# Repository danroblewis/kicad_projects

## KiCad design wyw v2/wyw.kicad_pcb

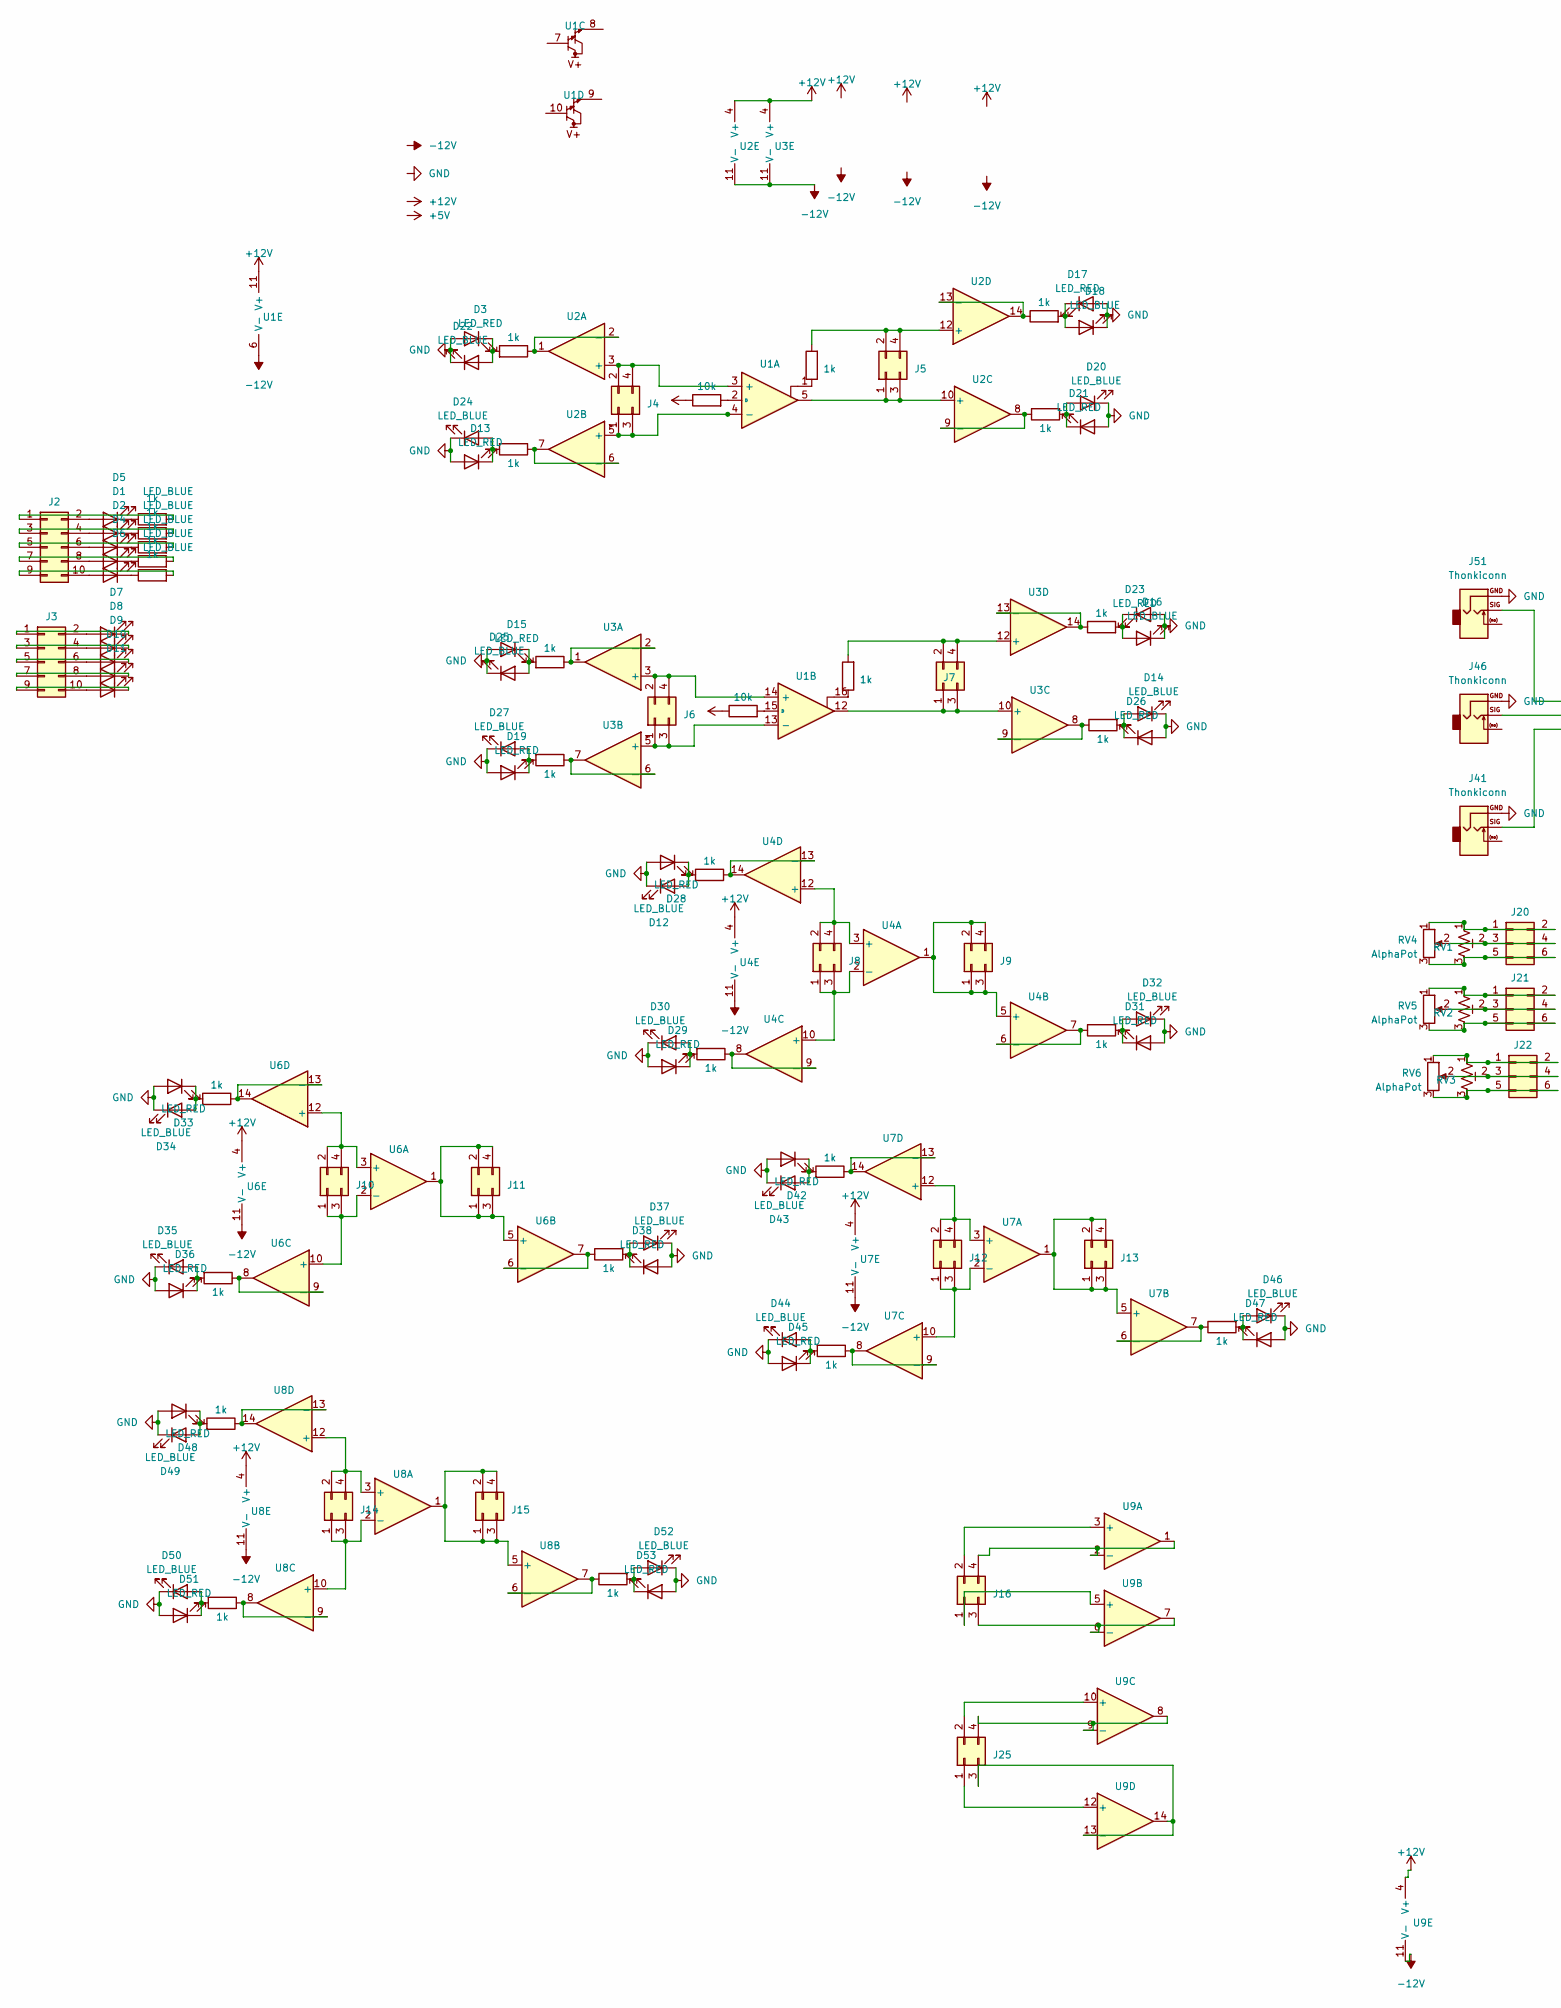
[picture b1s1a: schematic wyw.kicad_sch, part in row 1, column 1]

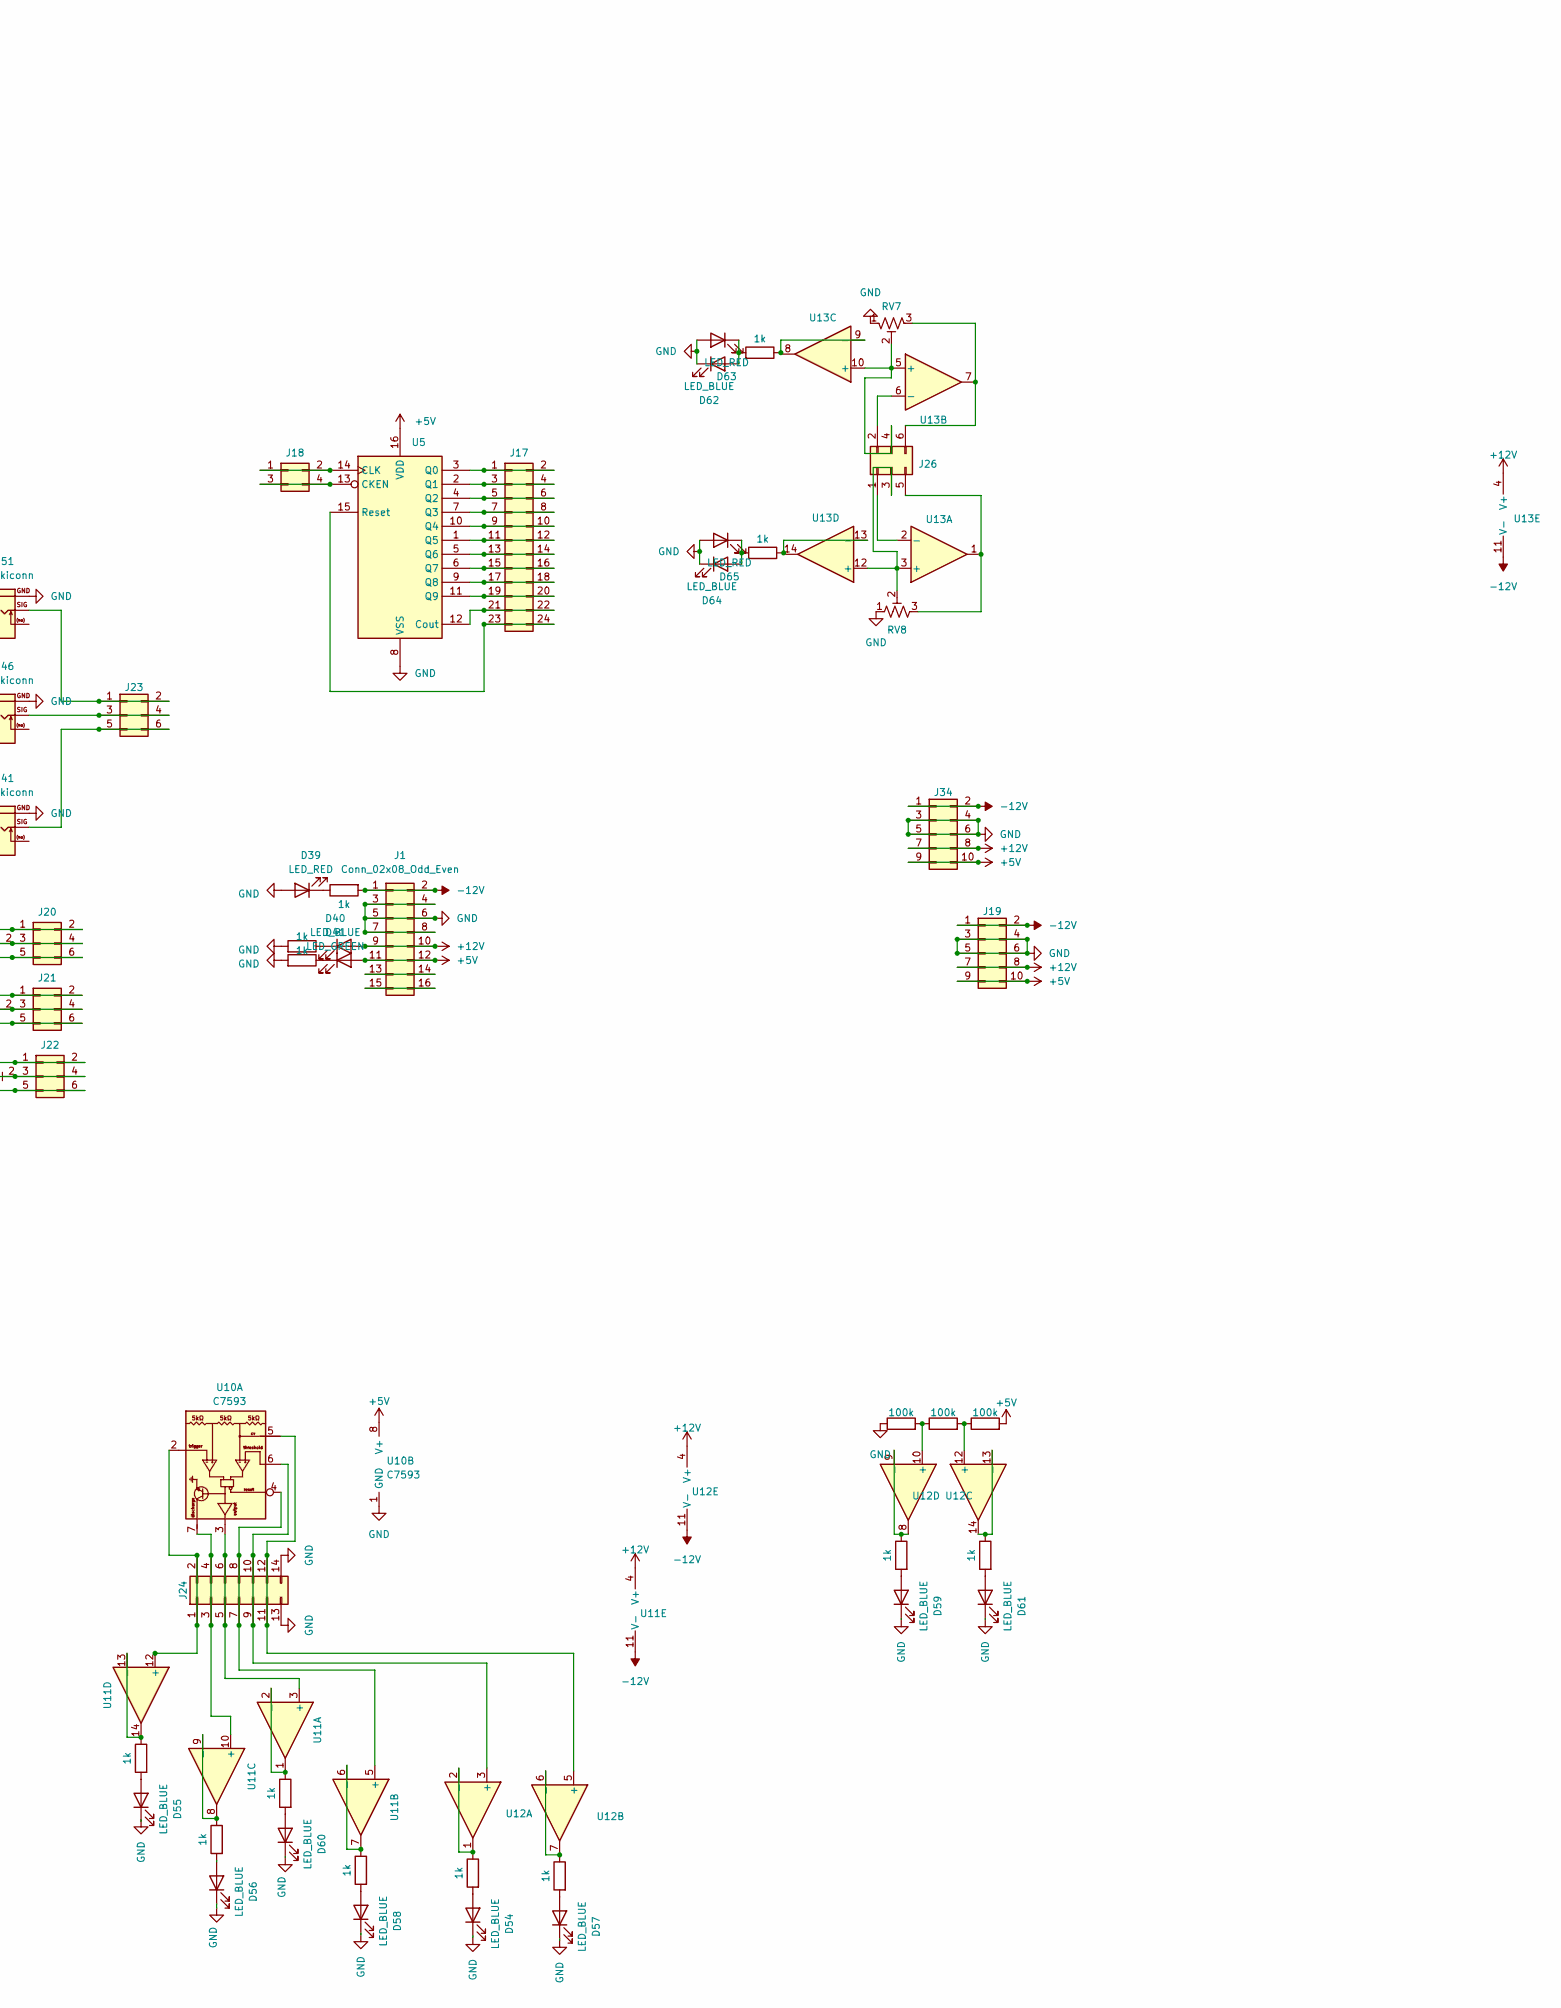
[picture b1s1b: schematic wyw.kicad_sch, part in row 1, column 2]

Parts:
D1, D2, D4, D5, D6, D7, D8, D9, D10, D11, D40: LED_BLUE; LED_0603_1608Metric; LCSC C72041
D3, D13, D15, D17, D19, D21, D23, D26, D28, D29, D31, D33, D36, D38, D42, D45, D47, D48, D51, D53, D63, D65: LED_RED; LED_0201_0603Metric; LCSC C3646921
D12, D14, D16, D18, D20, D22, D24, D25, D27, D30, D32, D34, D35, D37, D43, D44, D46, D49, D50, D52, D54, D55, D56, D57, D58, D59, D60, D61, D62, D64: LED_BLUE; LED_0201_0603Metric; LCSC C3646921
D39: LED_RED; LED_0603_1608Metric; LCSC C84263
D41: LED_GREEN; LED_0603_1608Metric; LCSC C72043
J1: Conn_02x08_Odd_Even; IDC-Header_2x08_P2.54mm_Vertical
J2, J3, J19, J34: 02x05; PinHeader_2x05_P2.54mm_Vertical_SMD; lcsc C261072
J4, J5, J6, J7, J8, J9, J10, J11, J12, J13, J14, J15, J16, J18, J25: 02x02; PinHeader_2x02_P2.54mm_Vertical_SMD; lcsc C3975147
J17: 02x12; PinHeader_2x12_P2.54mm_Vertical_SMD; lcsc C3975157
J20, J21, J22, J23, J26: 02x03; PinHeader_2x03_P2.54mm_Vertical_SMD; lcsc C3975148
J24: 02x07; PinHeader_2x07_P2.54mm_Vertical_SMD; lcsc C84005
J41, J46, J51: Thonkiconn; Jack_3.5mm_QingPu_WQP-PJ398SM_Vertical_CircularHoles
R1, R2, R3, R4, R5, R8, R9: 1k; R_0603_1608Metric; LCSC C21190
R6, R7: 10k; R_0603_1608Metric; lcsc C73809
R10, R11, R12, R13, R14, R15, R16, R17, R18, R19, R20, R21, R22, R23, R24, R25, R26, R27, R28, R29, R30, R31, R32, R33, R34, R35, R36, R37, R38, R42, R43, R44, R45: 1k; R_0603_1608Metric; lcsc C138165
R39, R40, R41: 100k; R_0603_1608Metric; LCSC C25803
RV1, RV2, RV3, RV7, RV8: R_Potentiometer_Trim_US; Potentiometer_Bourns_TC33X_Vertical; lcsc C128545
RV4, RV5, RV6: AlphaPot; Potentiometer_Alpha_RD901F-40-00D_Single_Vertical
U1: XL13700; SOP-16_3.9x9.9mm_P1.27mm; LCSC C521166
U2, U3, U4, U6, U7, U8, U9, U11, U12, U13: TL074; SOIC-14_3.9x8.7mm_P1.27mm; lcsc C6964
U5: 4017bm; SOP-16_3.9x9.9mm_P1.27mm; LCSC C356694
U10: NE555DR; SOIC-8-1EP_3.9x4.9mm_P1.27mm_EP2.29x3mm; LCSC C7593

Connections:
+5V: D41.2 (A), J1.11, J1.12, J19.9, J19.10, J34.9, J34.10, R41.2, U5.16 (VDD), U10.8 (V+)
+12V: D40.2 (A), J1.9, J1.10, J19.7, J19.8, J34.7, J34.8, R6.1, R7.1, U1.11 (V+), U2.4 (V+), U3.4 (V+), U4.4 (V+), U6.4 (V+), U7.4 (V+), U8.4 (V+), U9.4 (V+), U11.4 (V+), U12.4 (V+), U13.4 (V+)
-12V: J1.1, J1.2, J19.1, J19.2, J34.1, J34.2, R24.2, U1.6 (V-), U2.11 (V-), U3.11 (V-), U4.11 (V-), U6.11 (V-), U7.11 (V-), U8.11 (V-), U9.11 (V-), U11.11 (V-), U12.11 (V-), U13.11 (V-)
GND: D3.2 (A), D12.1 (K), D13.2 (A), D14.1 (K), D15.2 (A), D16.1 (K), D17.2 (A), D18.1 (K), D19.2 (A), D20.1 (K), D21.2 (A), D22.1 (K), D23.2 (A), D24.1 (K), D25.1 (K), D26.2 (A), D27.1 (K), D28.2 (A), D29.2 (A), D30.1 (K), D31.2 (A), D32.1 (K), D33.2 (A), D34.1 (K), D35.1 (K), D36.2 (A), D37.1 (K), D38.2 (A), D39.2 (A), D42.2 (A), D43.1 (K), D44.1 (K), D45.2 (A), D46.1 (K), D47.2 (A), D48.2 (A), D49.1 (K), D50.1 (K), D51.2 (A), D52.1 (K), D53.2 (A), D54.1 (K), D55.1 (K), D56.1 (K), D57.1 (K), D58.1 (K), D59.1 (K), D60.1 (K), D61.1 (K), D62.1 (K), D63.2 (A), D64.1 (K), D65.2 (A), J1.3, J1.4, J1.5, J1.6, J1.7, J1.8, J19.3, J19.4, J19.5, J19.6, J24.13, J24.14, J34.3, J34.4, J34.5, J34.6, J41.S, J46.S, J51.S, R25.2, R26.2, R39.1, RV7.1, RV8.1, U5.8 (VSS), U10.1 (GND)
unnamed: D1.2 (A), J2.4
unnamed: D1.1 (K), R1.1
unnamed: D2.2 (A), J2.6
unnamed: D2.1 (K), R2.1
unnamed: D4.2 (A), J2.8
unnamed: D4.1 (K), R4.1
unnamed: D5.2 (A), J2.2
unnamed: D5.1 (K), R3.1
unnamed: D6.2 (A), J2.10
unnamed: D6.1 (K), R5.1
unnamed: D7.2 (A), J3.2
unnamed: D7.1 (K), J3.1
unnamed: D8.2 (A), J3.4
unnamed: D8.1 (K), J3.3
unnamed: D9.2 (A), J3.6
unnamed: D9.1 (K), J3.5
unnamed: D10.2 (A), J3.8
unnamed: D10.1 (K), J3.7
unnamed: D11.2 (A), J3.10
unnamed: D11.1 (K), J3.9
unnamed: D12.2 (A), D28.1 (K), R18.2
unnamed: D13.1 (K), D24.2 (A), R11.2
unnamed: D14.2 (A), D26.1 (K), R17.2
unnamed: D15.1 (K), D25.2 (A), R12.2
unnamed: D16.2 (A), D23.1 (K), R16.2
unnamed: D17.1 (K), D18.2 (A), R13.2
unnamed: D19.1 (K), D27.2 (A), R14.2
unnamed: D20.2 (A), D21.1 (K), R15.2
unnamed: D3.1 (K), D22.2 (A), R10.2
unnamed: D29.1 (K), D30.2 (A), R19.2
unnamed: D31.1 (K), D32.2 (A), R20.2
unnamed: D33.1 (K), D34.2 (A), R21.2
unnamed: D35.2 (A), D36.1 (K), R22.2
unnamed: D37.2 (A), D38.1 (K), R23.2
unnamed: D39.1 (K), R24.1
unnamed: D40.1 (K), R25.1
unnamed: D41.1 (K), R26.1
unnamed: D42.1 (K), D43.2 (A), R27.2
unnamed: D44.2 (A), D45.1 (K), R28.2
unnamed: D46.2 (A), D47.1 (K), R29.2
unnamed: D48.1 (K), D49.2 (A), R30.2
unnamed: D50.2 (A), D51.1 (K), R31.2
unnamed: D52.2 (A), D53.1 (K), R32.2
unnamed: D54.2 (A), R37.2
unnamed: D55.2 (A), R33.2
unnamed: D56.2 (A), R34.2
unnamed: D57.2 (A), R38.2
unnamed: D58.2 (A), R35.2
unnamed: D59.2 (A), R42.2
unnamed: D60.2 (A), R36.2
unnamed: D61.2 (A), R43.2
unnamed: D62.2 (A), D63.1 (K), R44.2
unnamed: D64.2 (A), D65.1 (K), R45.2
unnamed: J1.13, J1.14
unnamed: J1.15, J1.16
unnamed: J2.1, R3.2
unnamed: J2.3, R1.2
unnamed: J2.5, R2.2
unnamed: J2.7, R4.2
unnamed: J2.9, R5.2
unnamed: J4.1, J4.3, U1.4 (-), U2.5 (+)
unnamed: J4.2, J4.4, U1.3 (+), U2.3 (+)
unnamed: J5.1, J5.3, U1.5, U2.10 (+)
unnamed: J5.2, J5.4, R9.2, U2.12 (+)
unnamed: J6.1, J6.3, U1.13 (-), U3.5 (+)
unnamed: J6.2, J6.4, U1.14 (+), U3.3 (+)
unnamed: J7.1, J7.3, U1.12, U3.10 (+)
unnamed: J7.2, J7.4, R8.2, U3.12 (+)
unnamed: J8.1, J8.3, U4.2 (-), U4.10 (+)
unnamed: J8.2, J8.4, U4.3 (+), U4.12 (+)
unnamed: J9.1, J9.2, J9.3, J9.4, U4.1, U4.5 (+)
unnamed: J10.1, J10.3, U6.2 (-), U6.10 (+)
unnamed: J10.2, J10.4, U6.3 (+), U6.12 (+)
unnamed: J11.1, J11.2, J11.3, J11.4, U6.1, U6.5 (+)
unnamed: J12.1, J12.3, U7.2 (-), U7.10 (+)
unnamed: J12.2, J12.4, U7.3 (+), U7.12 (+)
unnamed: J13.1, J13.2, J13.3, J13.4, U7.1, U7.5 (+)
unnamed: J14.1, J14.3, U8.2 (-), U8.10 (+)
unnamed: J14.2, J14.4, U8.3 (+), U8.12 (+)
unnamed: J15.1, J15.2, J15.3, J15.4, U8.1, U8.5 (+)
unnamed: J16.1, U9.5 (+)
unnamed: J16.2, U9.3 (+)
unnamed: J16.3, U9.6 (-), U9.7
unnamed: J16.4, U9.1, U9.2 (-)
unnamed: J17.1, J17.2, U5.3 (Q0)
unnamed: J17.3, J17.4, U5.2 (Q1)
unnamed: J17.5, J17.6, U5.4 (Q2)
unnamed: J17.7, J17.8, U5.7 (Q3)
unnamed: J17.9, J17.10, U5.10 (Q4)
unnamed: J17.11, J17.12, U5.1 (Q5)
unnamed: J17.13, J17.14, U5.5 (Q6)
unnamed: J17.15, J17.16, U5.6 (Q7)
unnamed: J17.17, J17.18, U5.9 (Q8)
unnamed: J17.19, J17.20, U5.11 (Q9)
unnamed: J17.21, J17.22, U5.12 (Cout)
unnamed: J17.23, J17.24, U5.15 (Reset)
unnamed: J18.1, J18.2, U5.14 (CLK)
unnamed: J18.3, J18.4, U5.13 (CKEN)
unnamed: J20.1, J20.2, RV1.1, RV4.1
unnamed: J20.3, J20.4, RV1.2, RV4.2
unnamed: J20.5, J20.6, RV1.3, RV4.3
unnamed: J21.1, J21.2, RV2.1, RV5.1
unnamed: J21.3, J21.4, RV2.2, RV5.2
unnamed: J21.5, J21.6, RV2.3, RV5.3
unnamed: J22.1, J22.2, RV3.1, RV6.1
unnamed: J22.3, J22.4, RV3.2, RV6.2
unnamed: J22.5, J22.6, RV3.3, RV6.3
unnamed: J23.1, J23.2, J51.T
unnamed: J23.3, J23.4, J46.T
unnamed: J23.5, J23.6, J41.T
unnamed: J24.1, J24.2, U10.2, U11.12 (+)
unnamed: J24.3, J24.4, U10.7, U11.10 (+)
unnamed: J24.5, J24.6, U10.3, U11.3 (+)
unnamed: J24.7, J24.8, U10.4, U11.5 (+)
unnamed: J24.9, J24.10, U10.6, U12.3 (+)
unnamed: J24.11, J24.12, U10.5, U12.5 (+)
unnamed: J25.1, U9.12 (+)
unnamed: J25.2, U9.10 (+)
unnamed: J25.3, U9.13 (-), U9.14
unnamed: J25.4, U9.8, U9.9 (-)
unnamed: J26.1, U13.2 (-)
unnamed: J26.2, U13.6 (-)
unnamed: J26.3, RV8.2, U13.3 (+), U13.12 (+)
unnamed: J26.4, RV7.2, U13.5 (+), U13.10 (+)
unnamed: J26.5, RV8.3, U13.1
unnamed: J26.6, RV7.3, U13.7
unnamed: R8.1, U1.16
unnamed: R9.1, U1.1
unnamed: R6.2, U1.2 (D)
unnamed: R7.2, U1.15 (D)
unnamed: R10.1, U2.1, U2.2 (-)
unnamed: R11.1, U2.6 (-), U2.7
unnamed: R15.1, U2.8, U2.9 (-)
unnamed: R13.1, U2.13 (-), U2.14
unnamed: R12.1, U3.1, U3.2 (-)
unnamed: R14.1, U3.6 (-), U3.7
unnamed: R17.1, U3.8, U3.9 (-)
unnamed: R16.1, U3.13 (-), U3.14
unnamed: R20.1, U4.6 (-), U4.7
unnamed: R19.1, U4.8, U4.9 (-)
unnamed: R18.1, U4.13 (-), U4.14
unnamed: R23.1, U6.6 (-), U6.7
unnamed: R22.1, U6.8, U6.9 (-)
unnamed: R21.1, U6.13 (-), U6.14
unnamed: R29.1, U7.6 (-), U7.7
unnamed: R28.1, U7.8, U7.9 (-)
unnamed: R27.1, U7.13 (-), U7.14
unnamed: R32.1, U8.6 (-), U8.7
unnamed: R31.1, U8.8, U8.9 (-)
unnamed: R30.1, U8.13 (-), U8.14
unnamed: R36.1, U11.1, U11.2 (-)
unnamed: R35.1, U11.6 (-), U11.7
unnamed: R34.1, U11.8, U11.9 (-)
unnamed: R33.1, U11.13 (-), U11.14
unnamed: R37.1, U12.1, U12.2 (-)
unnamed: R38.1, U12.6 (-), U12.7
unnamed: R39.2, R40.1, U12.10 (+)
unnamed: R42.1, U12.8, U12.9 (-)
unnamed: R40.2, R41.1, U12.12 (+)
unnamed: R43.1, U12.13 (-), U12.14
unnamed: R44.1, U13.8, U13.9 (-)
unnamed: R45.1, U13.13 (-), U13.14

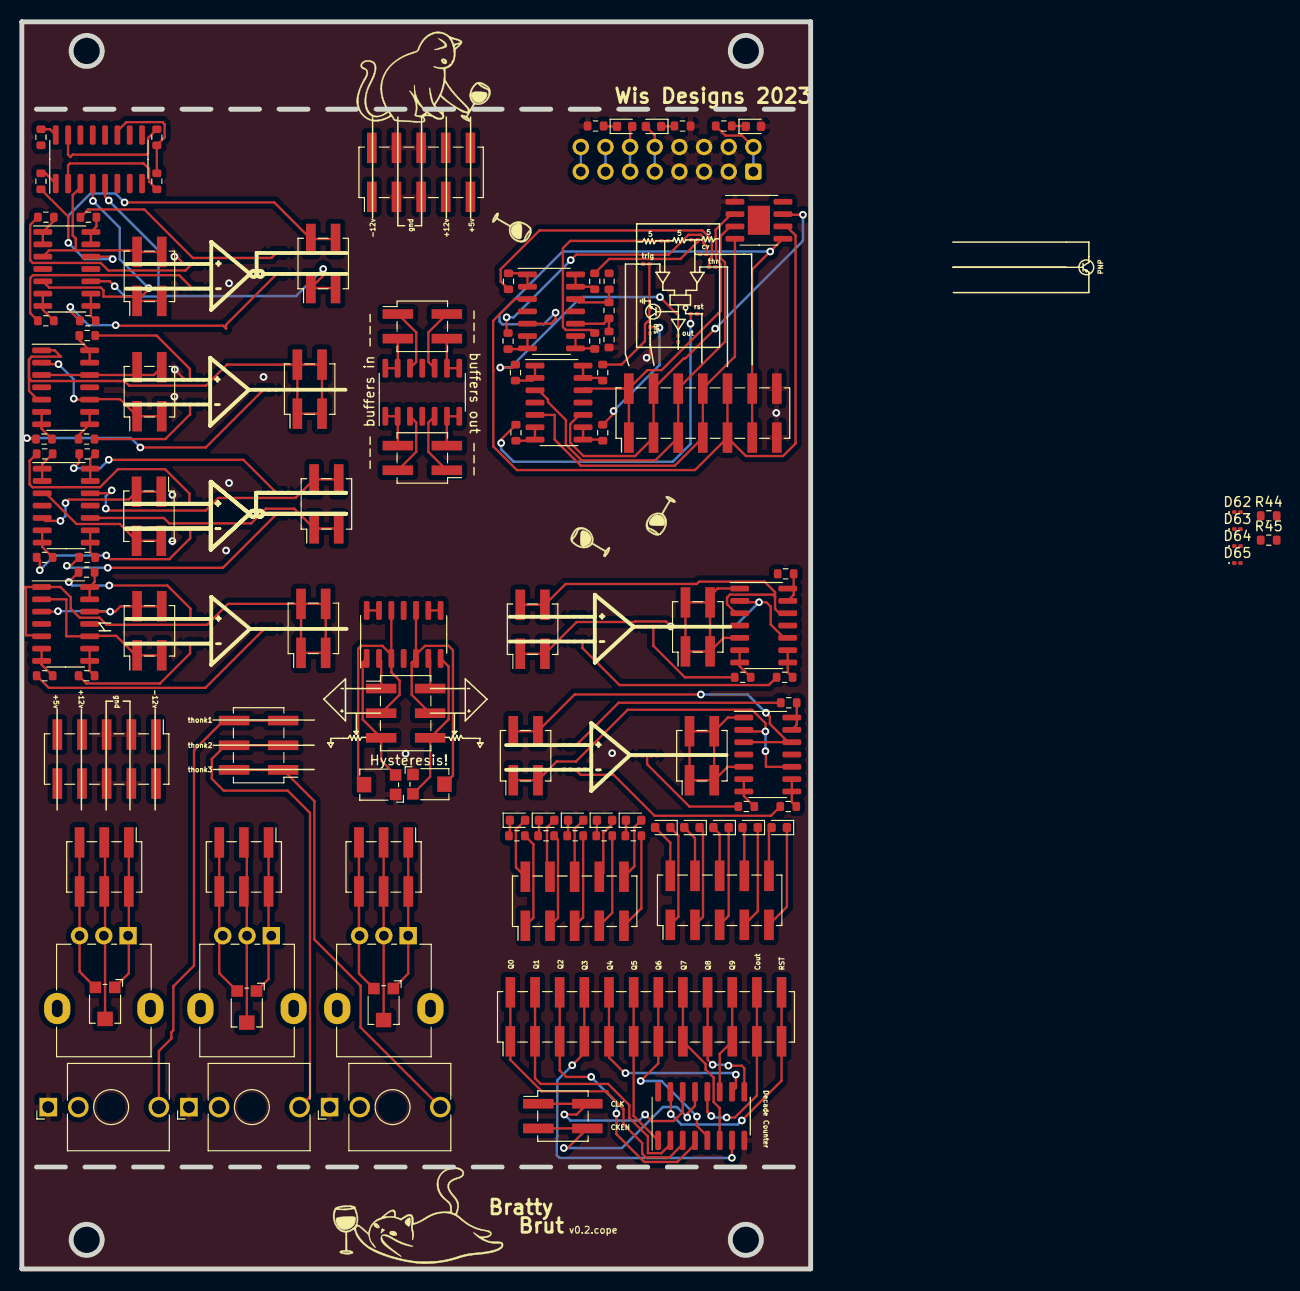
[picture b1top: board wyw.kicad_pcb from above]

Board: 2 copper layers, 81.3 x 128.5 mm, 161 parts (1 on the bottom side), 166 nets.

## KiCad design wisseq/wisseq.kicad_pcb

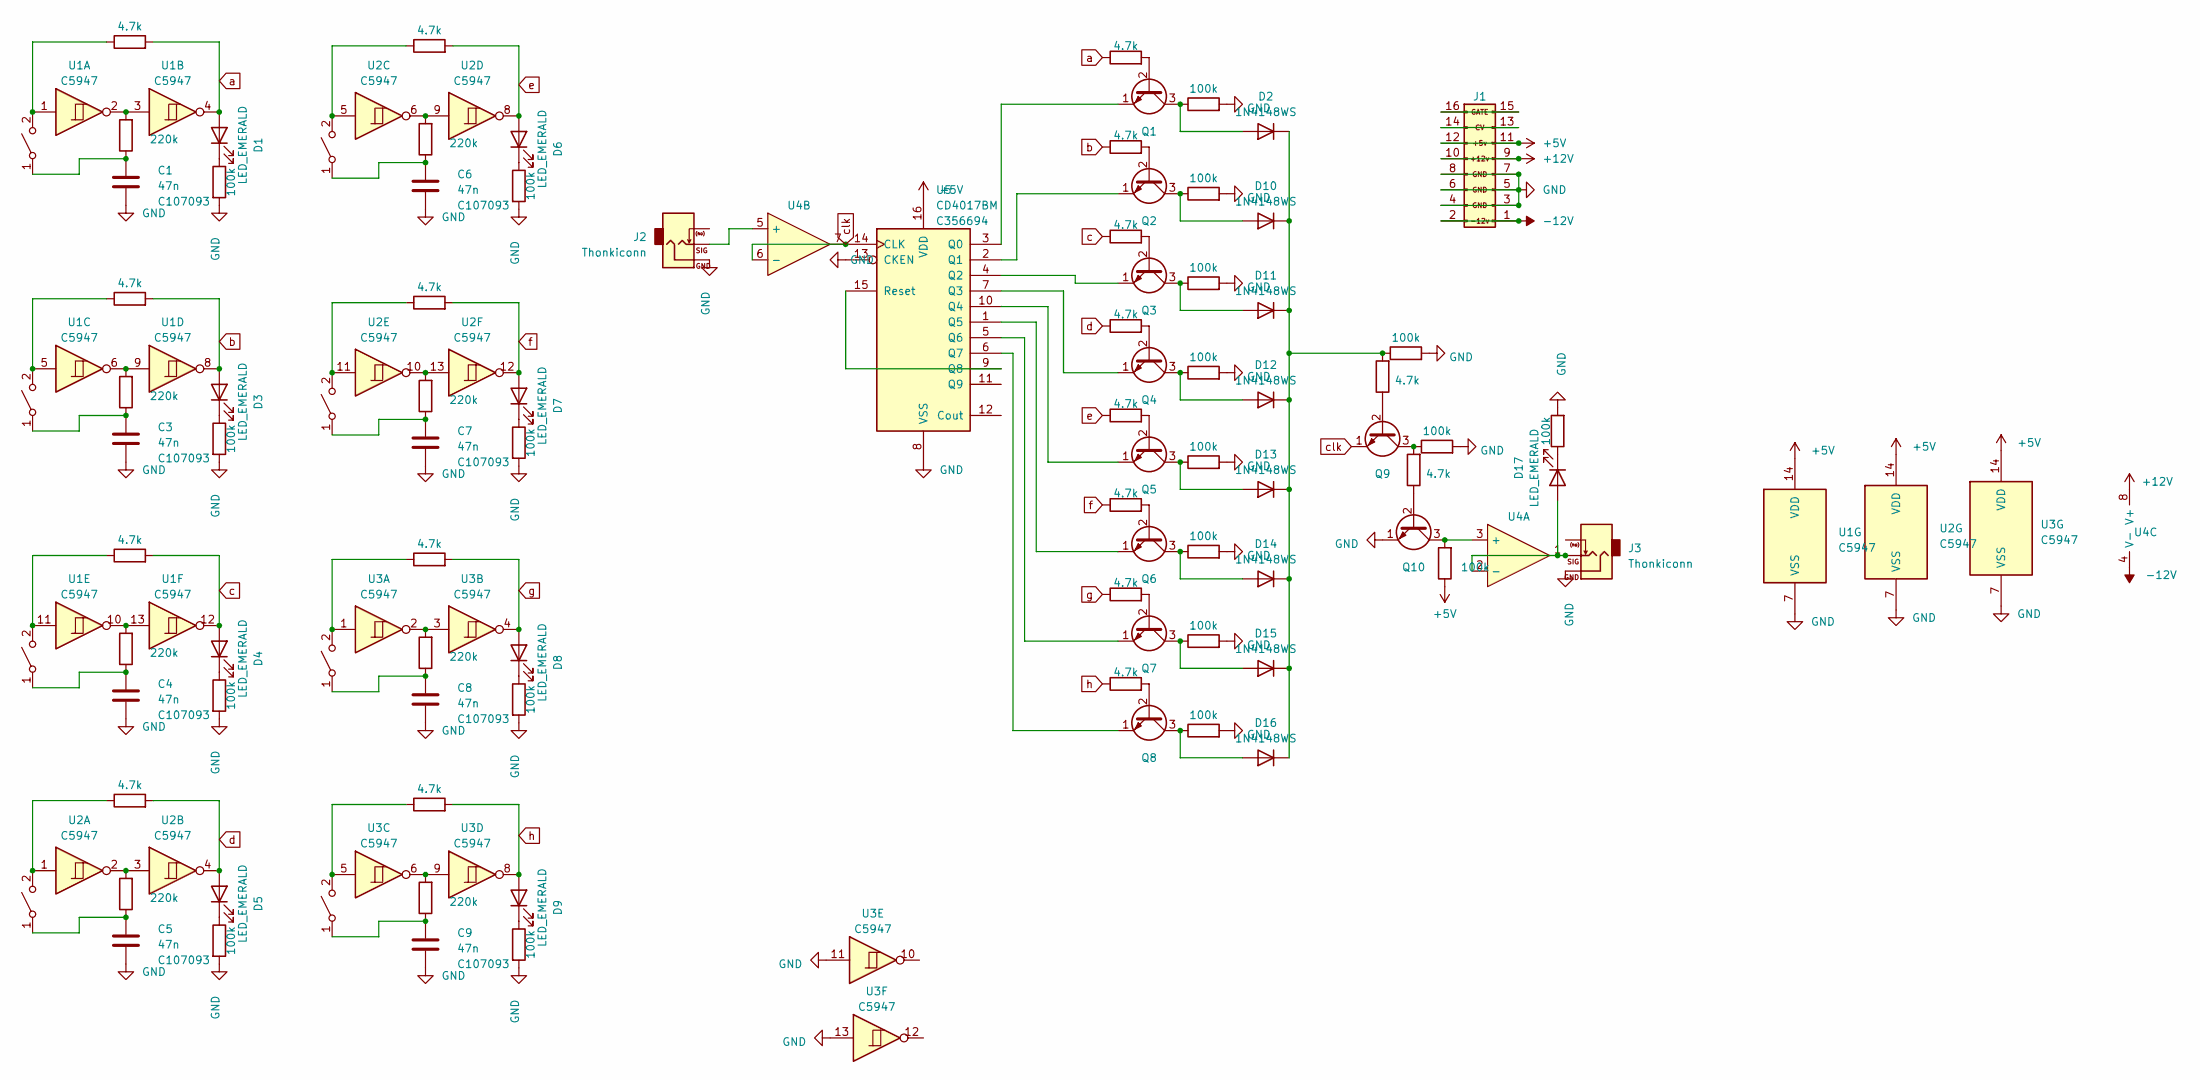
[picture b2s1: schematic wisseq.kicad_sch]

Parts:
C1, C3, C4, C5, C6, C7, C8, C9: 47n; C_0603_1608Metric; lcsc C107093
D1, D3, D4, D5, D6, D7, D8, D9, D17: LED_EMERALD; LED_0603_1608Metric; LCSC C72043
D2, D10, D11, D12, D13, D14, D15, D16: 1N4148WS; D_SOD-323; LCSC C2128
J1: EuroPower16; IDC-Header_2x08_P2.54mm_Vertical; lcsc C383608
J2, J3: Thonkiconn; Jack_3.5mm_QingPu_WQP-PJ398SM_Vertical_CircularHoles
Q1, Q2, Q3, Q4, Q5, Q6, Q7, Q8, Q9, Q10: 2N3904; SOT-23-3; lcsc C18536
R1, R7, R10, R13, R16, R19, R22, R25: 220k; R_0603_1608Metric; LCSC C217882
R2, R5, R6, R8, R11, R14, R17, R20, R23, R26, R29, R30, R33, R34, R35, R36, R42, R44: 4.7k; R_0603_1608Metric; LCSC C116693
R3, R4, R9, R12, R15, R18, R21, R24, R27, R28, R31, R32, R37, R38, R39, R40, R41, R43, R45, R46: 100k; R_0603_1608Metric; LCSC C25803
SW1, SW3, SW4, SW5, SW6, SW7, SW8, SW9: SW_SPST; SW_SPST_PTS645; lcsc C10852
U1, U2, U3: CD40106; SOIC-16_3.9x9.9mm_P1.27mm; lcsc C5947
U4: TL072; SOIC-8_3.9x4.9mm_P1.27mm; LCSC C6961
U5: CD4017BM; SOP-16_4.4x10.4mm_P1.27mm; lcsc C356694

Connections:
+5V: J1.11 (+5v_R), J1.12 (+5v_L), R45.1, U1.14 (VDD), U2.14 (VDD), U3.14 (VDD), U5.16 (VDD)
+12V: J1.9 (+12V_R), J1.10 (+12V_L), U4.8 (V+)
-12V: J1.1 (-12v_R), J1.2 (-12v_L), U4.4 (V-)
GND: C1.1, C3.1, C4.1, C5.1, C6.1, C7.1, C8.1, C9.1, J1.3 (GND), J1.4 (GND), J1.5 (GND_R3), J1.6 (GND_L3), J1.7 (GND_R2), J1.8 (GND_L2), J2.S, J3.S, Q10.1 (E), R3.2, R4.2, R9.2, R12.2, R15.2, R18.2, R21.2, R24.2, R27.2, R28.2, R31.2, R32.2, R37.2, R38.2, R39.2, R40.2, R41.2, R43.2, R46.2, U1.7 (VSS), U2.7 (VSS), U3.7 (VSS), U3.11, U3.13, U5.8 (VSS), U5.13 (CKEN)
unnamed: D1.1 (K), R3.1
unnamed: D2.2 (A), Q1.3 (C), R4.1
unnamed: D3.1 (K), R9.1
unnamed: D4.1 (K), R12.1
unnamed: D5.1 (K), R15.1
unnamed: D6.1 (K), R18.1
unnamed: D7.1 (K), R21.1
unnamed: D8.1 (K), R24.1
unnamed: D9.1 (K), R27.1
unnamed: D10.2 (A), Q2.3 (C), R28.1
unnamed: D2.1 (K), D10.1 (K), D11.1 (K), D12.1 (K), D13.1 (K), D14.1 (K), D15.1 (K), D16.1 (K), R41.1, R42.2
unnamed: D11.2 (A), Q3.3 (C), R31.1
unnamed: D12.2 (A), Q4.3 (C), R32.1
unnamed: D13.2 (A), Q5.3 (C), R37.1
unnamed: D14.2 (A), Q6.3 (C), R38.1
unnamed: D15.2 (A), Q7.3 (C), R39.1
unnamed: D16.2 (A), Q8.3 (C), R40.1
unnamed: D17.2 (A), J3.T, U4.1, U4.2 (-)
unnamed: D17.1 (K), R46.1
unnamed: J1.13 (CV_R), J1.14 (CV_L)
unnamed: J1.15 (GATE_R), J1.16 (GATE_L)
unnamed: Q1.2 (B), R5.2
unnamed: Q1.1 (E), U5.3 (Q0)
unnamed: Q2.2 (B), R6.2
unnamed: Q2.1 (E), U5.2 (Q1)
unnamed: Q3.2 (B), R29.2
unnamed: Q3.1 (E), U5.4 (Q2)
unnamed: Q4.2 (B), R30.2
unnamed: Q4.1 (E), U5.7 (Q3)
unnamed: Q5.2 (B), R33.2
unnamed: Q5.1 (E), U5.10 (Q4)
unnamed: Q6.2 (B), R34.2
unnamed: Q6.1 (E), U5.1 (Q5)
unnamed: Q7.2 (B), R35.2
unnamed: Q7.1 (E), U5.5 (Q6)
unnamed: Q8.2 (B), R36.2
unnamed: Q8.1 (E), U5.6 (Q7)
unnamed: Q9.2 (B), R42.1
unnamed: Q9.3 (C), R43.1, R44.2
unnamed: Q10.2 (B), R44.1
unnamed: Q10.3 (C), R45.2, U4.3 (+)
unnamed: R1.2, U1.2, U1.3
unnamed: R7.2, U1.6, U1.9
unnamed: R10.2, U1.10, U1.13
unnamed: R13.2, U2.2, U2.3
unnamed: R16.2, U2.6, U2.9
unnamed: R19.2, U2.10, U2.13
unnamed: R22.2, U3.2, U3.3
unnamed: R25.2, U3.6, U3.9
unnamed: C1.2, R1.1, SW1.1 (A)
unnamed: R2.1, SW1.2 (B), U1.1
unnamed: C3.2, R7.1, SW3.1 (A)
unnamed: R8.1, SW3.2 (B), U1.5
unnamed: C4.2, R10.1, SW4.1 (A)
unnamed: R11.1, SW4.2 (B), U1.11
unnamed: C5.2, R13.1, SW5.1 (A)
unnamed: R14.1, SW5.2 (B), U2.1
unnamed: C6.2, R16.1, SW6.1 (A)
unnamed: R17.1, SW6.2 (B), U2.5
unnamed: C7.2, R19.1, SW7.1 (A)
unnamed: R20.1, SW7.2 (B), U2.11
unnamed: C8.2, R22.1, SW8.1 (A)
unnamed: R23.1, SW8.2 (B), U3.1
unnamed: C9.2, R25.1, SW9.1 (A)
unnamed: R26.1, SW9.2 (B), U3.5
unnamed: J2.T, U4.5 (+)
unnamed: U5.9 (Q8), U5.15 (Reset)
a: D1.2 (A), R2.2, R5.1, U1.4
b: D3.2 (A), R6.1, R8.2, U1.8
c: D4.2 (A), R11.2, R29.1, U1.12
clk: Q9.1 (E), U4.6 (-), U4.7, U5.14 (CLK)
d: D5.2 (A), R14.2, R30.1, U2.4
e: D6.2 (A), R17.2, R33.1, U2.8
f: D7.2 (A), R20.2, R34.1, U2.12
g: D8.2 (A), R23.2, R35.1, U3.4
h: D9.2 (A), R26.2, R36.1, U3.8

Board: 2 copper layers, 96 parts (0 on the bottom side), 71 nets, no tracks yet.

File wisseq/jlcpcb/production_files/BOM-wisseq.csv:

Comment,Designator,Footprint,LCSC
47n,"C1,C3,C4,C5,C6,C7,C8,C9",C_0603_1608Metric,C107093
SW_SPST,"SW1,SW3,SW4,SW5,SW6,SW7,SW8,SW9",SW_SPST_PTS645,C10852
4.7k,"R11,R14,R17,R2,R20,R23,R26,R29,R30,R33,R34,R35,R36,R42,R44,R5,R6,R8",R_0603_1608Metric,C116693
2N3904,"Q1,Q10,Q2,Q3,Q4,Q5,Q6,Q7,Q8,Q9",SOT-23-3,C18536
1N4148WS,"D10,D11,D12,D13,D14,D15,D16,D2",D_SOD-323,C2128
220k,"R1,R10,R13,R16,R19,R22,R25,R7",R_0603_1608Metric,C217882
100k,"R12,R15,R18,R21,R24,R27,R28,R3,R31,R32,R37,R38,R39,R4,R40,R41,R43,R45,R46,R9",R_0603_1608Metric,C25803
CD4017BM,U5,SOP-16_4.4x10.4mm_P1.27mm,C356694
EuroPower16,J1,IDC-Header_2x08_P2.54mm_Vertical,C383608
CD40106,"U1,U2,U3",SOIC-16_3.9x9.9mm_P1.27mm,C5947
TL072,U4,SOIC-8_3.9x4.9mm_P1.27mm,C6961
LED_EMERALD,"D1,D17,D3,D4,D5,D6,D7,D8,D9",LED_0603_1608Metric,C72043

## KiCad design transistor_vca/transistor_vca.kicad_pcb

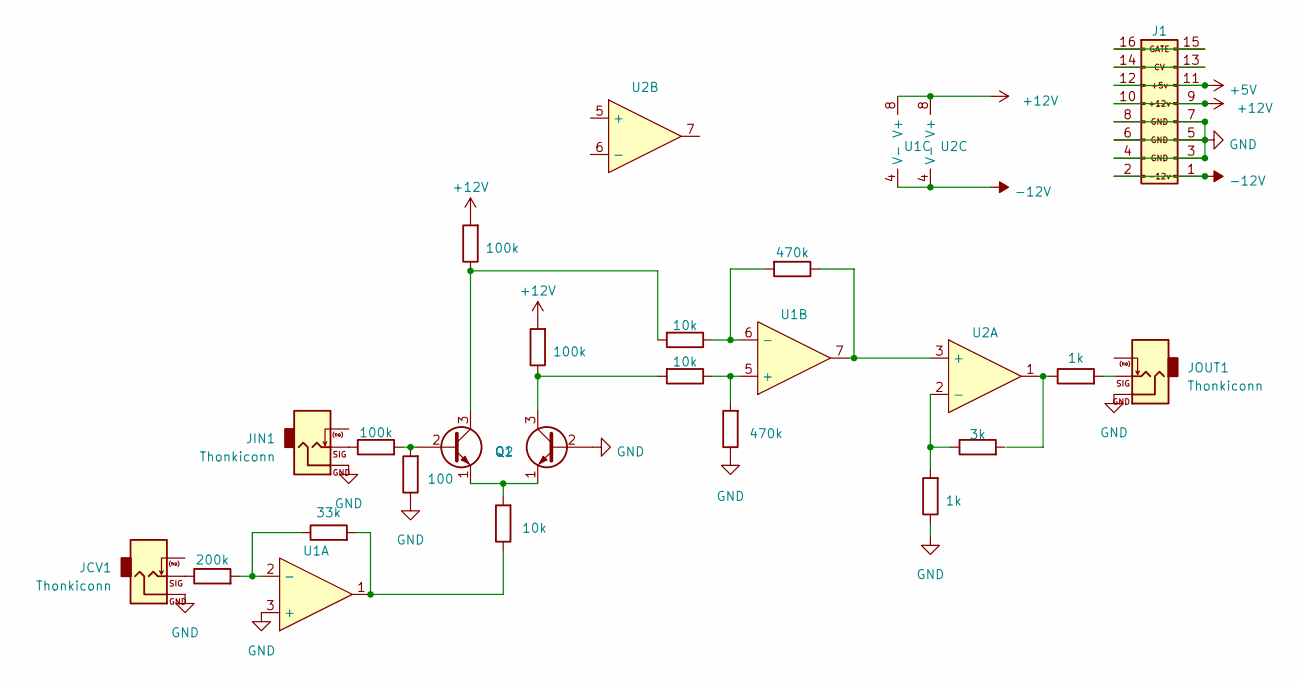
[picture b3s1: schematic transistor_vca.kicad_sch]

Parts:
J1: EuroPower16; IDC-Header_2x08_P2.54mm_Vertical_SMD; lcsc C383608
JCV1: Thonkiconn; Jack_3.5mm_QingPu_WQP-PJ398SM_Vertical_CircularHoles
JIN1: Thonkiconn; Jack_3.5mm_QingPu_WQP-PJ398SM_Vertical_CircularHoles
JOUT1: Thonkiconn; Jack_3.5mm_QingPu_WQP-PJ398SM_Vertical_CircularHoles
Q1, Q2: 2N3904; SOT-23-3; lcsc C18536
R1, R7, R8: 10k; R_0603_1608Metric; lcsc C73809
R2: 33k; R_0603_1608Metric; LCSC C4216
R3: 200k; R_0603_1608Metric; lcsc C144683
R4, R5, R6: 100k; R_0603_1608Metric; LCSC C25803
R9: 100; R_0603_1608Metric; lcsc C86983
R10, R11: 1k; R_0603_1608Metric; LCSC C21190
R12: 3k; R_0603_1608Metric; LCSC C73812
R13, R14: 470k; R_0603_1608Metric; lcsc C115418
U1, U2: TL072; SOIC-8_3.9x4.9mm_P1.27mm; LCSC C67473

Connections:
+5V: J1.11 (+5v_R), J1.12 (+5v_L)
+12V: J1.9 (+12V_R), J1.10 (+12V_L), R5.2, R6.2, U1.8 (V+), U2.8 (V+)
-12V: J1.1 (-12v_R), J1.2 (-12v_L), U1.4 (V-), U2.4 (V-)
GND: J1.3 (GND), J1.4 (GND), J1.5 (GND_R3), J1.6 (GND_L3), J1.7 (GND_R2), J1.8 (GND_L2), JCV1.S, JIN1.S, JOUT1.S, Q2.2 (B), R9.1, R11.1, R13.1, U1.3 (+)
unnamed: J1.13 (CV_R), J1.14 (CV_L)
unnamed: J1.15 (GATE_R), J1.16 (GATE_L)
unnamed: JCV1.T, R3.1
unnamed: JIN1.T, R4.1
unnamed: JOUT1.T, R10.2
unnamed: Q1.2 (B), R4.2, R9.2
unnamed: Q1.3 (C), R5.1, R8.2
unnamed: Q1.1 (E), Q2.1 (E), R1.2
unnamed: Q2.3 (C), R6.1, R7.2
unnamed: R1.1, R2.2, U1.1
unnamed: R10.1, U2.1
unnamed: R2.1, R3.2, U1.2 (-)
unnamed: R7.1, R13.2, U1.5 (+)
unnamed: R8.1, R14.2, U1.6 (-)
unnamed: R14.1, U1.7, U2.3 (+)
unnamed: R11.2, R12.1, U2.2 (-)

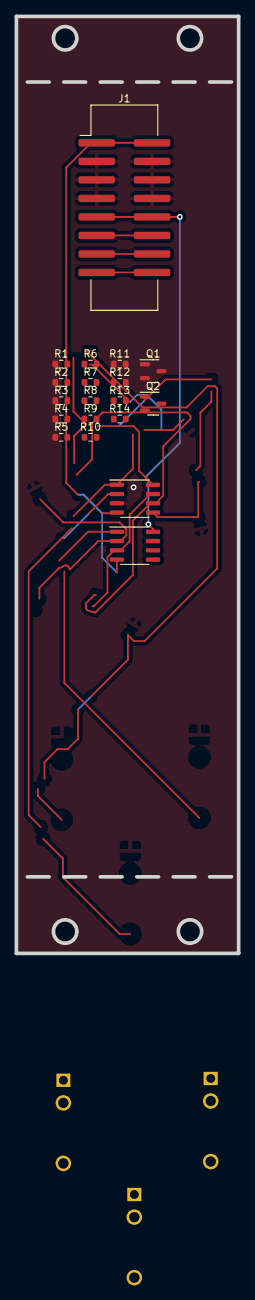
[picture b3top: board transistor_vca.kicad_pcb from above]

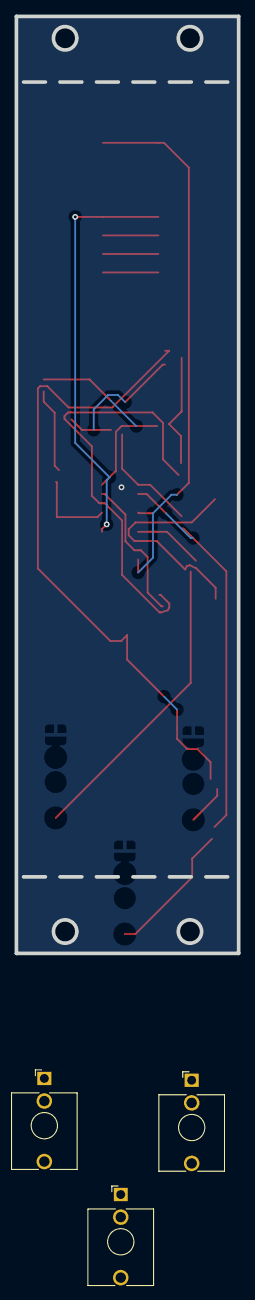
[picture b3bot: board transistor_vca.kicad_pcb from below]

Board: 2 copper layers, 30.5 x 128.5 mm, 22 parts (3 on the bottom side), 20 nets.
